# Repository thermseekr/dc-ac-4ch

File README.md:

# DC-AC-4CH

Triac board with 4x 24 VDC inputs and 4x 220 AC outputs.

## LICENSE

This project is licensed under the [Creative Commons BY-NC 4.0 License](https://creativecommons.org/licenses/by-nc/4.0/).
Commercial use is not permitted without prior written consent. See the [LICENSE.txt](LICENSE.txt) file for details.

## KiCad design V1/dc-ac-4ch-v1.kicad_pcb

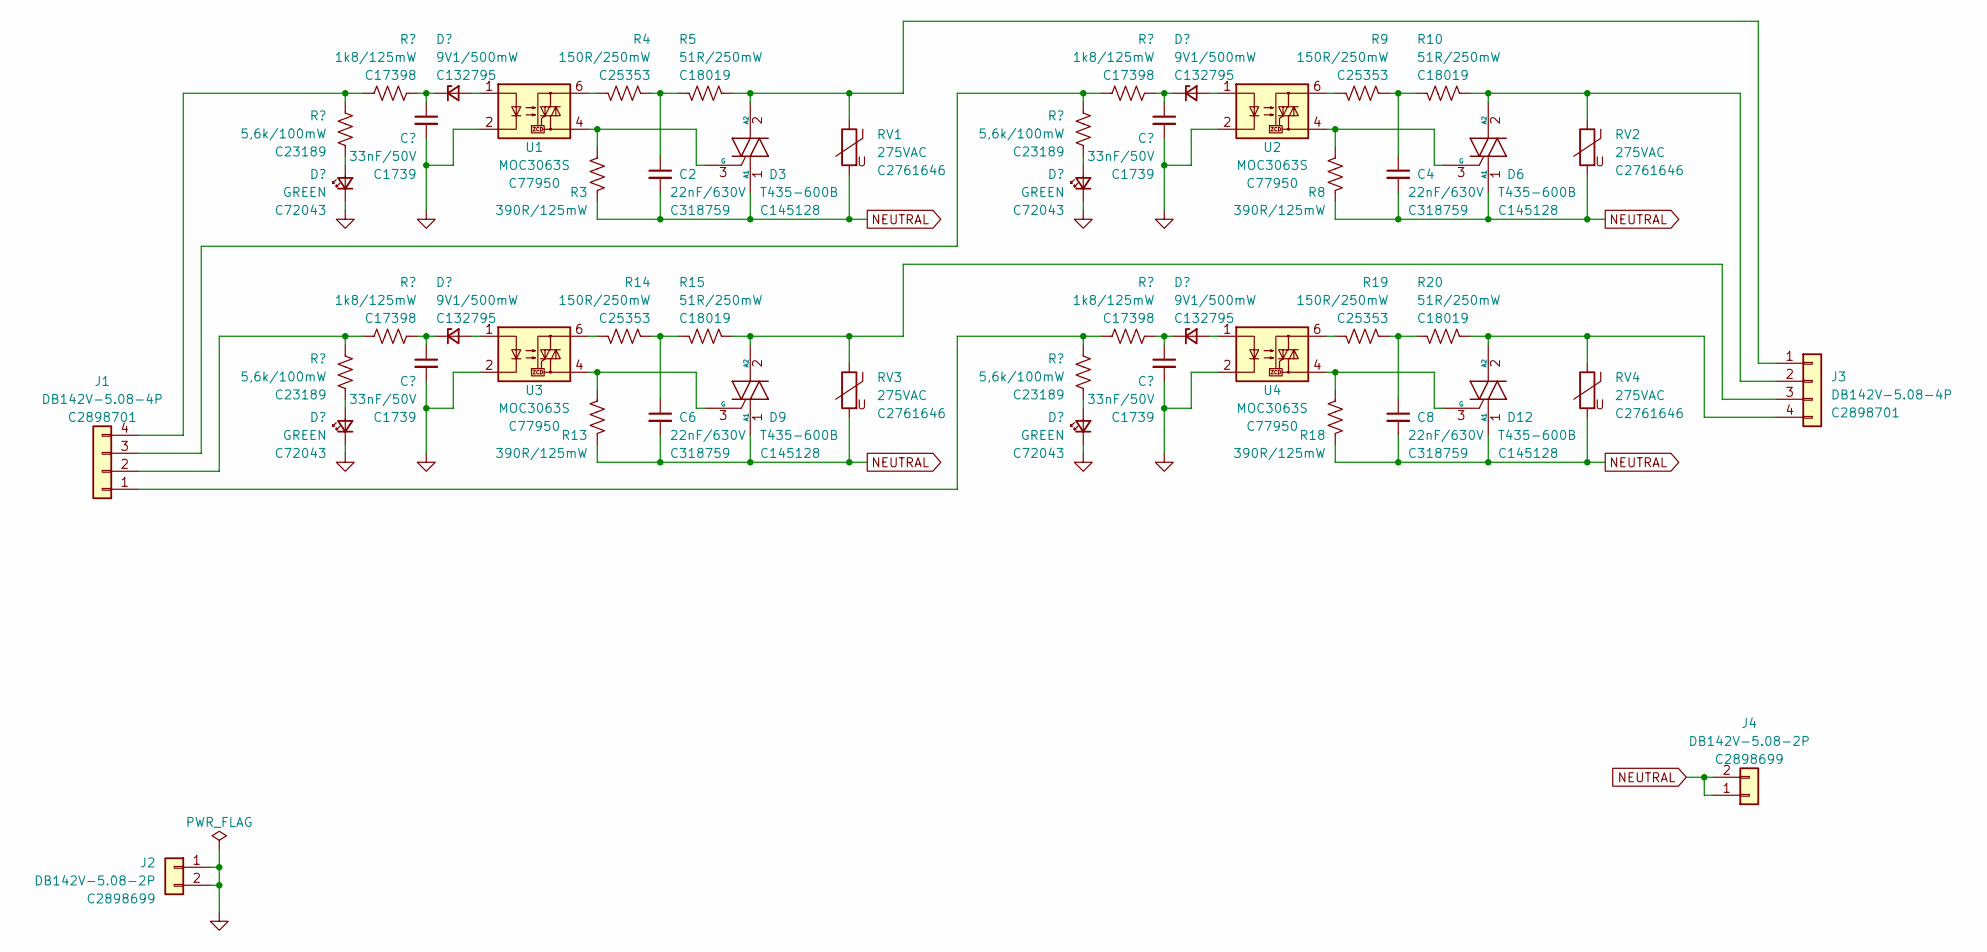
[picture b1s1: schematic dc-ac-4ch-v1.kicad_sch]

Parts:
C1, C3, C5, C7: 33nF/50V; C_0805_2012Metric; LCSC Part # C1739
C2, C4, C6, C8: 22nF/630V; C_1206_3216Metric; Mfr Part # CL31B223KHHNNNE; JLCPCB BOM 1
D1, D4, D7, D10: GREEN; LED_0603_1608Metric; Mfr Part # 19-217/GHC-YR1S2/3T; LCSC Part # C72043
D2, D5, D8, D11: 9V1/500mW; D_SOD-123; Mfr Part # MMSZ9V1T1G; JLCPCB BOM 1
D3, D6, D9, D12: T435-600B; TO-252-2; Mfr Part # T435-600B-TR; JLCPCB BOM 1
J1, J3: DB142V-5.08-4P; TerminalBlock_Dibo_DB142V-5.08-4P_1x04_P5.08mm_Vertical; Mfr Part # DB142V-5.08-4P; JLCPCB BOM 1
J2, J4: DB142V-5.08-2P; TerminalBlock_Dibo_DB142V-5.08-2P_1x02_P5.08mm_Vertical; Mfr Part # DB142V-5.08-2P; JLCPCB BOM 1
R1, R6, R11, R16: 5,6k/100mW; R_0603_1608Metric; Mfr Part # 0603WAF5601T5E; LCSC Part # C23189
R2, R7, R12, R17: 1k8/125mW; R_0805_2012Metric; Mfr Part # 0805W8F1801T5E; LCSC Part # C17398
R3, R8, R13, R18: 390R/125mW; R_0805_2012Metric; Mfr Part # 0805W8F3900T5E; JLCPCB BOM 1
R4, R9, R14, R19: 150R/250mW; R_1206_3216Metric; Mfr Part # 1206W4J0151T5E; JLCPCB BOM 1
R5, R10, R15, R20: 51R/250mW; R_1206_3216Metric; Mfr Part # 1206W4F510JT5E; JLCPCB BOM 1
RV1, RV2, RV3, RV4: 275VAC; RV_Disc_D9.50mm_W3.6mm_P5.08mm; Mfr Part # RM07D431KC1IE100; JLCPCB BOM 1
U1, U2, U3, U4: MOC3063S; SMDIP-6_W9.53mm_Clearance8mm; Mfr Part # MOC3063S-TA1; JLCPCB BOM 1

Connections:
GND: C1.2, C3.2, C5.2, C7.2, D1.1 (K), D4.1 (K), D7.1 (K), D10.1 (K), J2.1, J2.2, U1.2, U2.2, U3.2, U4.2
NEUTRAL: C2.2, C4.2, C6.2, C8.2, D3.1 (A1), D6.1 (A1), D9.1 (A1), D12.1 (A1), J4.1, J4.2, R3.2, R8.2, R13.2, R18.2, RV1.2, RV2.2, RV3.2, RV4.2
unnamed: C2.1, R4.1, R5.2
unnamed: C4.1, R9.1, R10.2
unnamed: C6.1, R14.1, R15.2
unnamed: C8.1, R19.1, R20.2
unnamed: D1.2 (A), R1.2
unnamed: D2.2 (A), U1.1
unnamed: C1.1, D2.1 (K), R2.1
unnamed: D3.2 (A2), J3.1, R5.1, RV1.1
unnamed: D3.3 (G), R3.1, U1.4
unnamed: D4.2 (A), R6.2
unnamed: D5.2 (A), U2.1
unnamed: C3.1, D5.1 (K), R7.1
unnamed: D6.2 (A2), J3.2, R10.1, RV2.1
unnamed: D6.3 (G), R8.1, U2.4
unnamed: D7.2 (A), R11.2
unnamed: D8.2 (A), U3.1
unnamed: C5.1, D8.1 (K), R12.1
unnamed: D9.2 (A2), J3.3, R15.1, RV3.1
unnamed: D9.3 (G), R13.1, U3.4
unnamed: D10.2 (A), R16.2
unnamed: D11.2 (A), U4.1
unnamed: C7.1, D11.1 (K), R17.1
unnamed: D12.2 (A2), J3.4, R20.1, RV4.1
unnamed: D12.3 (G), R18.1, U4.4
unnamed: J1.1, R16.1, R17.2
unnamed: J1.2, R11.1, R12.2
unnamed: J1.3, R6.1, R7.2
unnamed: J1.4, R1.1, R2.2
unnamed: R4.2, U1.6
unnamed: R9.2, U2.6
unnamed: R14.2, U3.6
unnamed: R19.2, U4.6

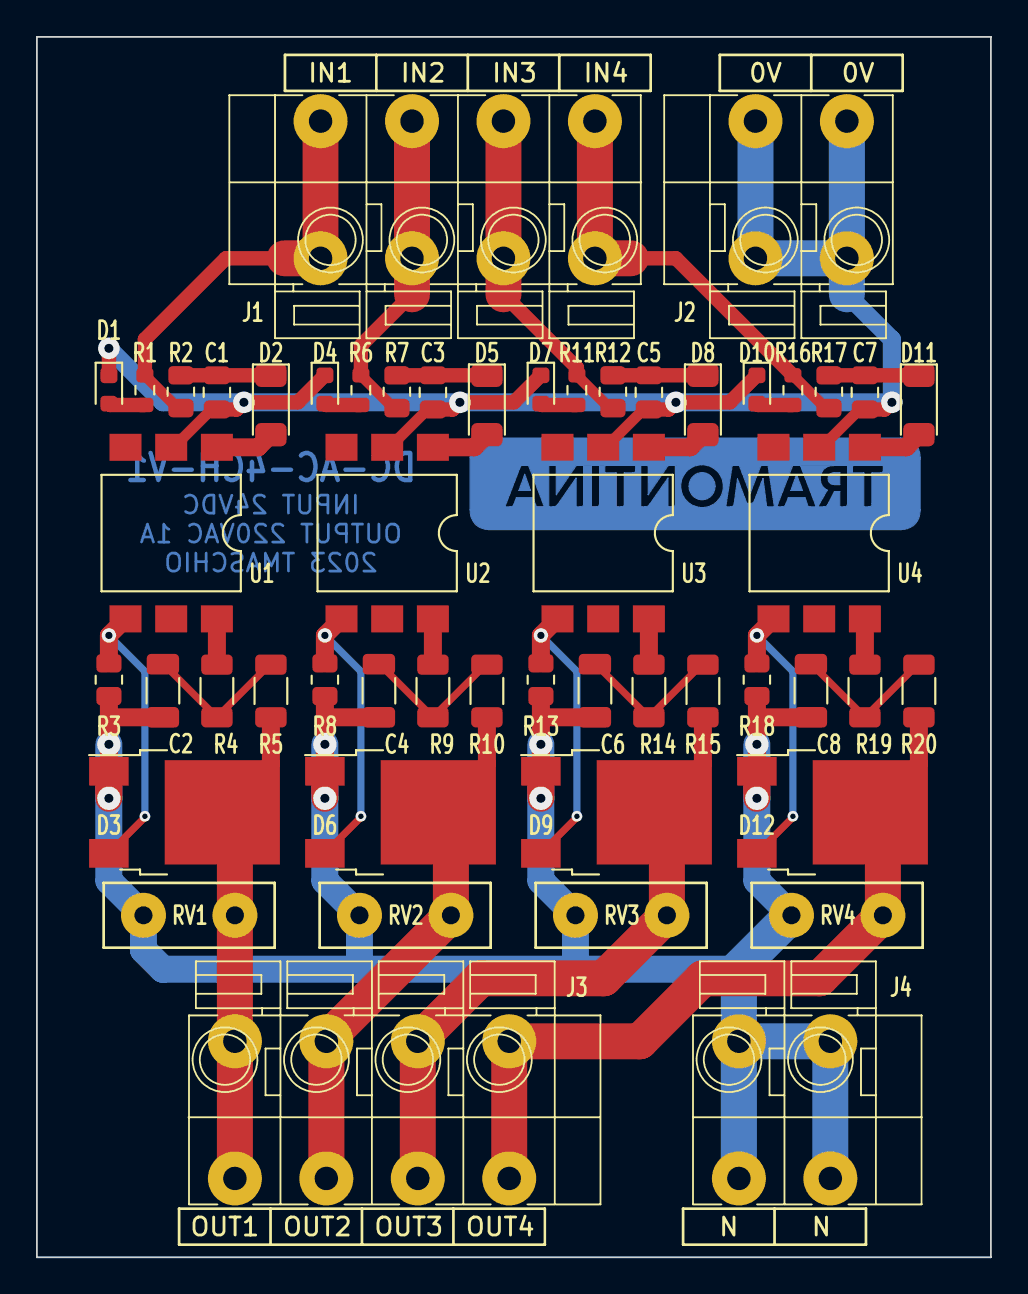
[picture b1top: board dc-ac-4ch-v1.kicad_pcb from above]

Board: 2 copper layers, 53.0 x 67.8 mm, 52 parts (0 on the bottom side), 34 nets.

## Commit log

2023-09-06 Initialize repo
2023-09-06 Place missing track under zone
2023-09-08 Rename files
2023-09-08 Repo cleanup
2023-09-08 Design completed.
2023-09-15 Final tweaks for production
2025-06-29 Added license
